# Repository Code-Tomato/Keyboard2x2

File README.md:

# 2x2 Keyboard

## Overview
This is a 2x2 keyboard I made to get experience using KiCAD.

## Features
- Uses the atmega32u4 chip
- Arranges by rows and columns starting from 0

## Getting Started
### Prerequisites
Download the latest version of KiCAD. [Download KiCAD](https://www.kicad.org/download/)

In the future, I will be developing the drivers through QMK.

### Installation
Clone the project into your device and open the .kicad files

## Part List
Here are the parts I used for this build.

| Index | DigiKey Part #                     | Manufacturer Part Number | Description                        | Quantity | Unit Price | Extended Price |
|-------|------------------------------------|--------------------------|------------------------------------|----------|------------|----------------|
| 1     | 478-KGM21NR71H104MTCT-ND           | KGM21NR71H104MT          | CAP CER 0.1UF 50V X7R 0805         | 3        | $0.16      | $0.48          |
| 2     | 1276-6455-1-ND                     | CL21A106KOQNNNG          | CAP CER 10UF 16V X5R 0805          | 1        | $0.10      | $0.10          |
| 3     | 1276-1066-1-ND                     | CL21B105KAFNNNE          | CAP CER 1UF 25V X7R 0805           | 1        | $0.10      | $0.10          |
| 4     | 1276-2605-1-ND                     | CL21C220JB61PNC          | CAP CER 22PF 50V C0G/NP0 0805      | 2        | $0.15      | $0.30          |
| 5     | 1N4148WTPMSCT-ND                   | 1N4148W-TP               | DIODE GEN PURP 100V 150MA SOD123   | 4        | $0.12      | $0.48          |
| 6     | 507-1803-1-ND                      | 0ZCJ0050AF2E             | PTC RESET FUSE 24V 500MA 1206      | 1        | $0.24      | $0.24          |
| 7     | P10KDACT-ND                        | ERA-6AEB103V             | RES SMD 10K OHM 0.1% 1/8W 0805     | 2        | $0.32      | $0.64          |
| 8     | P22ACT-ND                          | ERJ-6GEYJ220V            | RES SMD 22 OHM 5% 1/8W 0805        | 2        | $0.10      | $0.20          |
| 9     | CKN10361CT-ND                      | RS-187R05A2-DS MT RT     | SWITCH TACTILE SPST-NO 0.05A 12V   | 1        | $0.68      | $0.68          |
| 10    | ATMEGA32U4-AU-ND                   | ATMEGA32U4-AU            | IC MCU 8BIT 32KB FLASH 44TQFP      | 1        | $5.29      | $5.29          |
| 11    | WM3895CT-ND                        | 0548190589               | CONN RCPT MINI USB B 5POS SMD RA   | 1        | $1.55      | $1.55          |
| 12    | 478-CX3225SB16000D0GZJC1CT-ND      | CX3225SB16000D0GZJC1     | CRYSTAL 16.0000MHZ 8PF SMD         | 1        | $0.62      | $0.62          |
|       |                                    |                          |                                    |          |            | **Subtotal**   |
|       |                                    |                          |                                    |          |            | **$10.68**     |

Make sure you get your preferred key switches and keycaps for this build.

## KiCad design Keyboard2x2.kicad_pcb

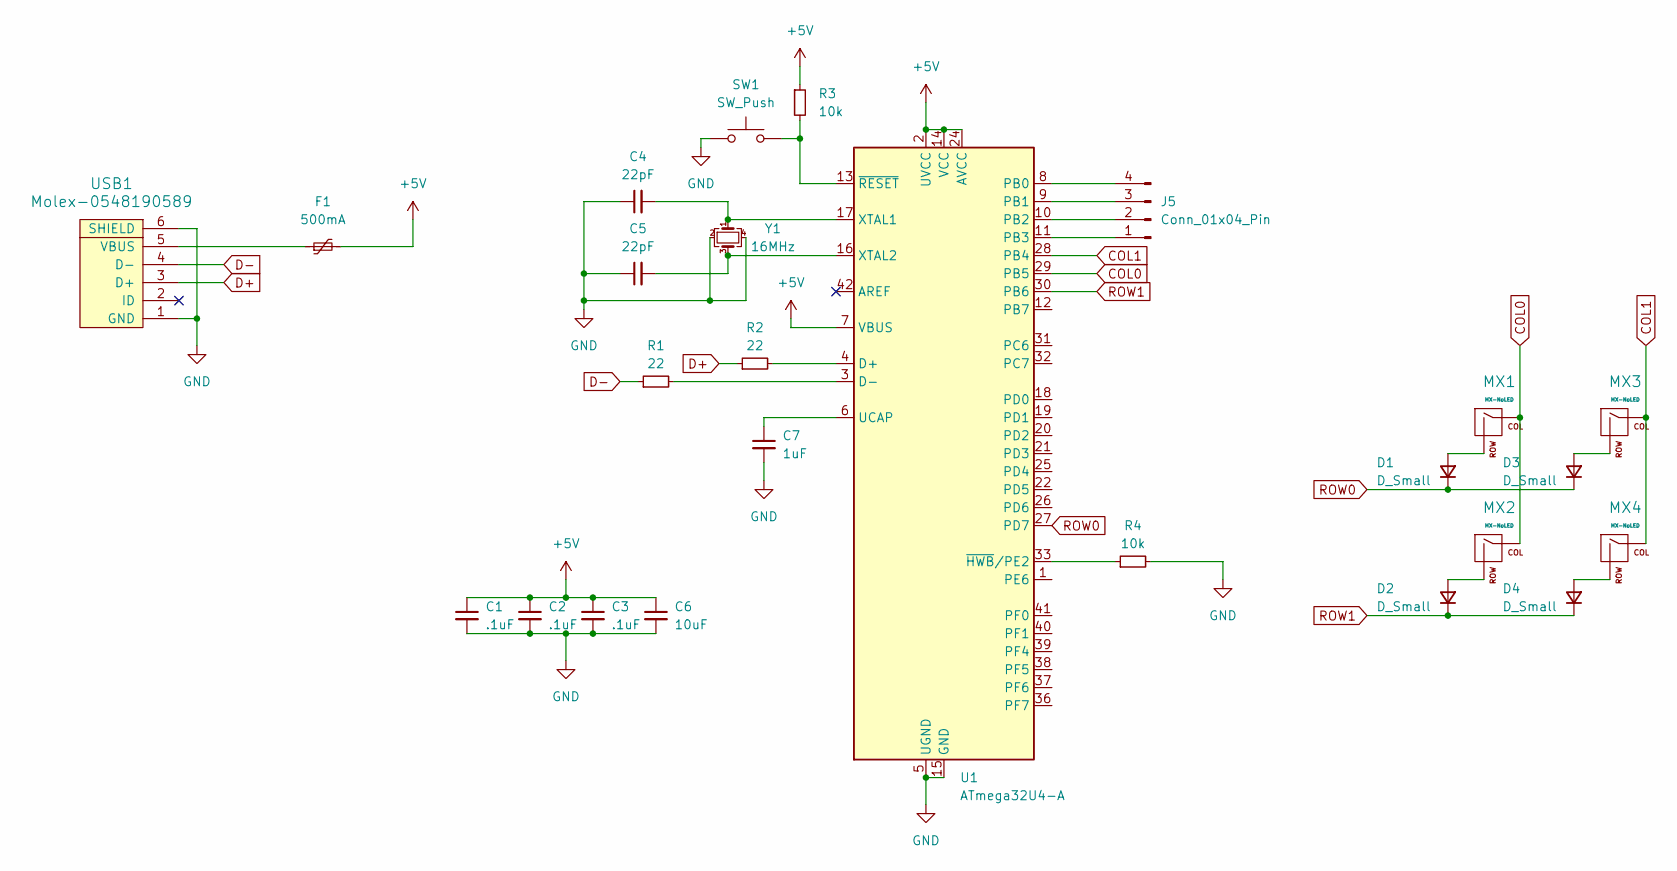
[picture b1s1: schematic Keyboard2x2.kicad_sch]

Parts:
C1, C2, C3: .1uF; C_0805_2012Metric
C4, C5: 22pF; C_0805_2012Metric
C6: 10uF; C_0805_2012Metric
C7: 1uF; C_0805_2012Metric
D1, D2, D3, D4: D_Small; D_SOD-123
F1: 500mA; Fuse_1206_3216Metric
J5: Conn_01x04_Pin; PinHeader_1x04_P1.00mm_Vertical
MX1, MX2, MX3, MX4: MX-NoLED; MX-1U
R1, R2: 22; R_0805_2012Metric
R3, R4: 10k; R_0805_2012Metric
SW1: SW_Push; SKQG-1155865
U1: ATmega32U4-A; TQFP-44_10x10mm_P0.8mm
USB1: Molex-0548190589
Y1: 16MHz; Crystal_SMD_3225-4Pin_3.2x2.5mm

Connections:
+5V: C1.1, C2.1, C3.1, C6.1, F1.2, R3.1, U1.2 (UVCC), U1.7 (VBUS), U1.14 (VCC), U1.24 (AVCC), U1.34 (VCC), U1.44 (AVCC)
COL0: MX1.1 (COL), MX2.1 (COL), U1.29 (PB5)
COL1: MX3.1 (COL), MX4.1 (COL), U1.28 (PB4)
D+: R2.1, USB1.3 (D+)
D-: R1.1, USB1.4 (D-)
GND: C1.2, C2.2, C3.2, C4.1, C5.1, C6.2, C7.2, R4.2, SW1.1, U1.5 (UGND), U1.15 (GND), U1.23 (GND), U1.35 (GND), U1.43 (GND), USB1.1 (GND), USB1.6 (SHIELD), Y1.2, Y1.4
unnamed: D1.2 (A), MX1.2 (ROW)
unnamed: D2.2 (A), MX2.2 (ROW)
unnamed: D3.2 (A), MX3.2 (ROW)
unnamed: D4.2 (A), MX4.2 (ROW)
unnamed: J5.1, U1.11 (PB3)
unnamed: J5.2, U1.10 (PB2)
unnamed: J5.3, U1.9 (PB1)
unnamed: J5.4, U1.8 (PB0)
unnamed: R2.2, U1.4 (D+)
unnamed: R1.2, U1.3 (D-)
unnamed: C7.1, U1.6 (UCAP)
unnamed: C4.2, U1.17 (XTAL1), Y1.1
unnamed: C5.2, U1.16 (XTAL2), Y1.3
unnamed: R4.1, U1.33 (~HWB/PE2)
unnamed: R3.2, SW1.2, U1.13 (~RESET)
unnamed: F1.1, USB1.5 (VBUS)
ROW0: D1.1 (K), D3.1 (K), U1.27 (PD7)
ROW1: D2.1 (K), D4.1 (K), U1.30 (PB6)

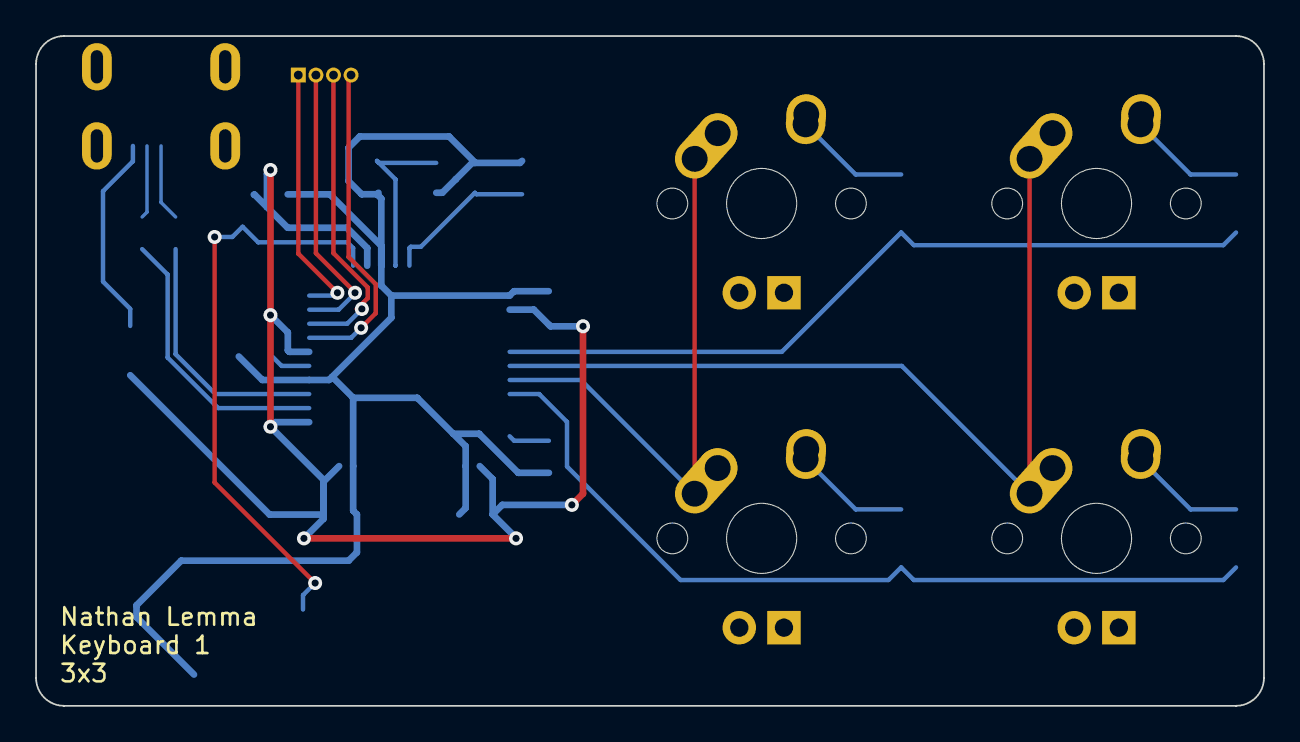
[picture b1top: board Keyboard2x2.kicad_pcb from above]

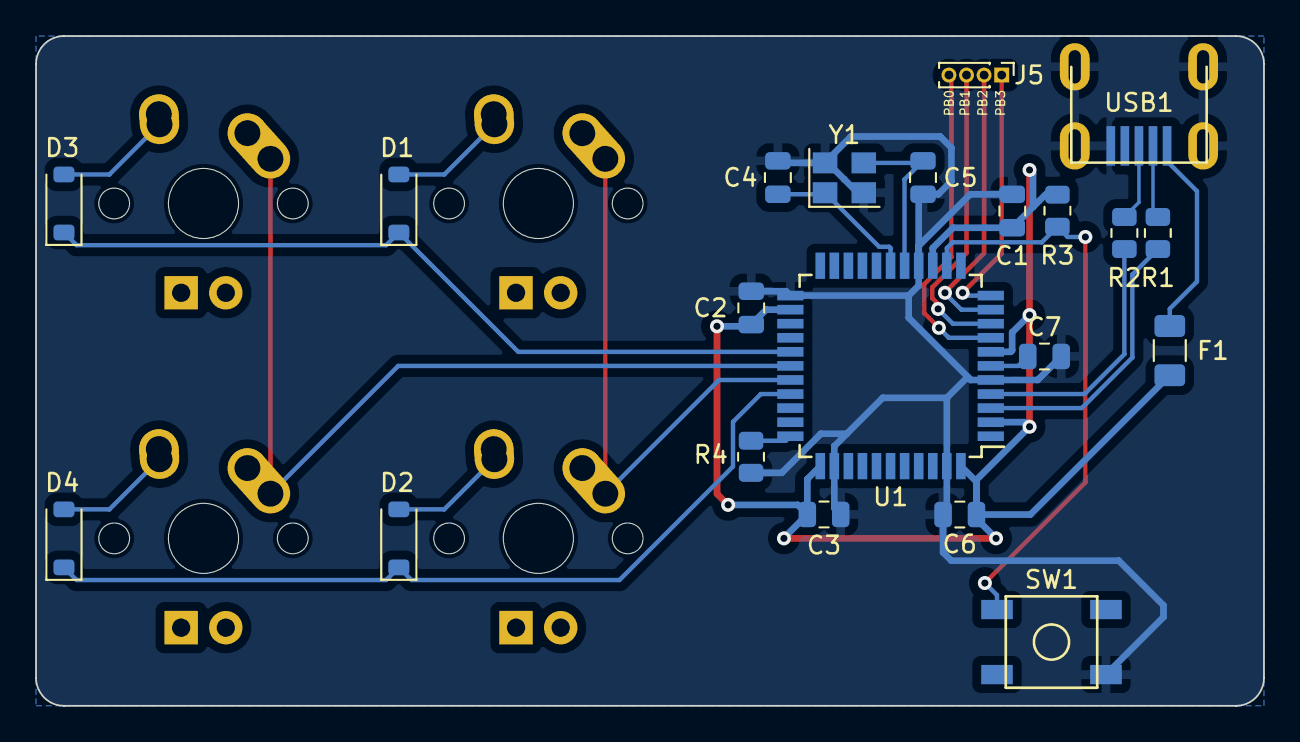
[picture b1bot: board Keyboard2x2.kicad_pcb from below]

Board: 2 copper layers, 69.8 x 38.1 mm, 25 parts (21 on the bottom side), 24 nets.

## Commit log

2024-01-01 New file
2024-01-01 Add submodules
2024-01-01 Configuation of the project
2024-01-01 1/1/2024: Chosen MCU
2024-01-02 1/2/2024: Completed wiring
2024-01-03 1/2/2024: Finished and printed
2024-01-10 Small update
2024-01-15 added pictures
2024-01-31 Revision 2 of the keyboard
2024-01-31 renamed
2024-01-31 compressed gerbers
